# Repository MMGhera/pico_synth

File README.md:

# pico_synth

A small hybrid synthesizer: a Raspberry Pi Pico 2 W generates the waveforms and envelopes digitally, and the sound runs through an analog VCA and filter before reaching the line output.

Designed in KiCad 10. **Status:** PCBs and parts ordered, firmware not written yet. The first version is a single voice.

## How it works

- **Oscillators and envelopes** run in firmware on the RP2350. Sine, square, triangle and sawtooth are selectable, and 4 LEDs show the active waveform.
- **Control voltages** come from an MCP4728 and are level-shifted by a TL074H to drive the OTAs.
- **The analog section** runs from ±5 V generated on the board by a TPS65133 from the Pico's VSYS.
- **8 knobs** (Attack, Decay, Sustain, Release, Cutoff, Resonance, Envelope, Volume) are read through a 74HC4051 mux into the Pico's ADC.
- **Display header** for a 4-pin I²C OLED.
- **Line-level output** for active speakers. There is no onboard power amp.

## Boards

| Board | Layers | Size | Notes |
|---|---|---|---|
| Main (`synth_pico.kicad_pro`) | 4 (GND plane on In1, power on In2) | 160 × 78 mm | Powered over the Pico's USB |
| Keyboard (`keyboard/`) | 2 | ~170 × 105 mm | 12 keys (one octave) + 4 function buttons, Cherry MX–compatible switches, 4×4 diode matrix |

The boards connect through a 10-pin 2.54 mm header and an F-F Dupont ribbon:

| Pin | 1 | 2–5 | 6–9 | 10 |
|---|---|---|---|---|
| Signal | GND | ROW0–3 | COL0–3 | 3V3 (not used by the keyboard) |

The function buttons are octave down, octave up, waveform select, and one spare(will probably implement octave up/down here too).

## Notes

- The pot net names in the schematic (`POT_xxx`) don't match the silkscreen labels. The knob order was changed late, and the knob-to-mux-channel mapping is handled in firmware.
- The BOM lists a PCM5102A, but the PCM5101A (and PCM5100A) are pin-compatible drop-in replacements.

---

made by Mihnea Gherasim

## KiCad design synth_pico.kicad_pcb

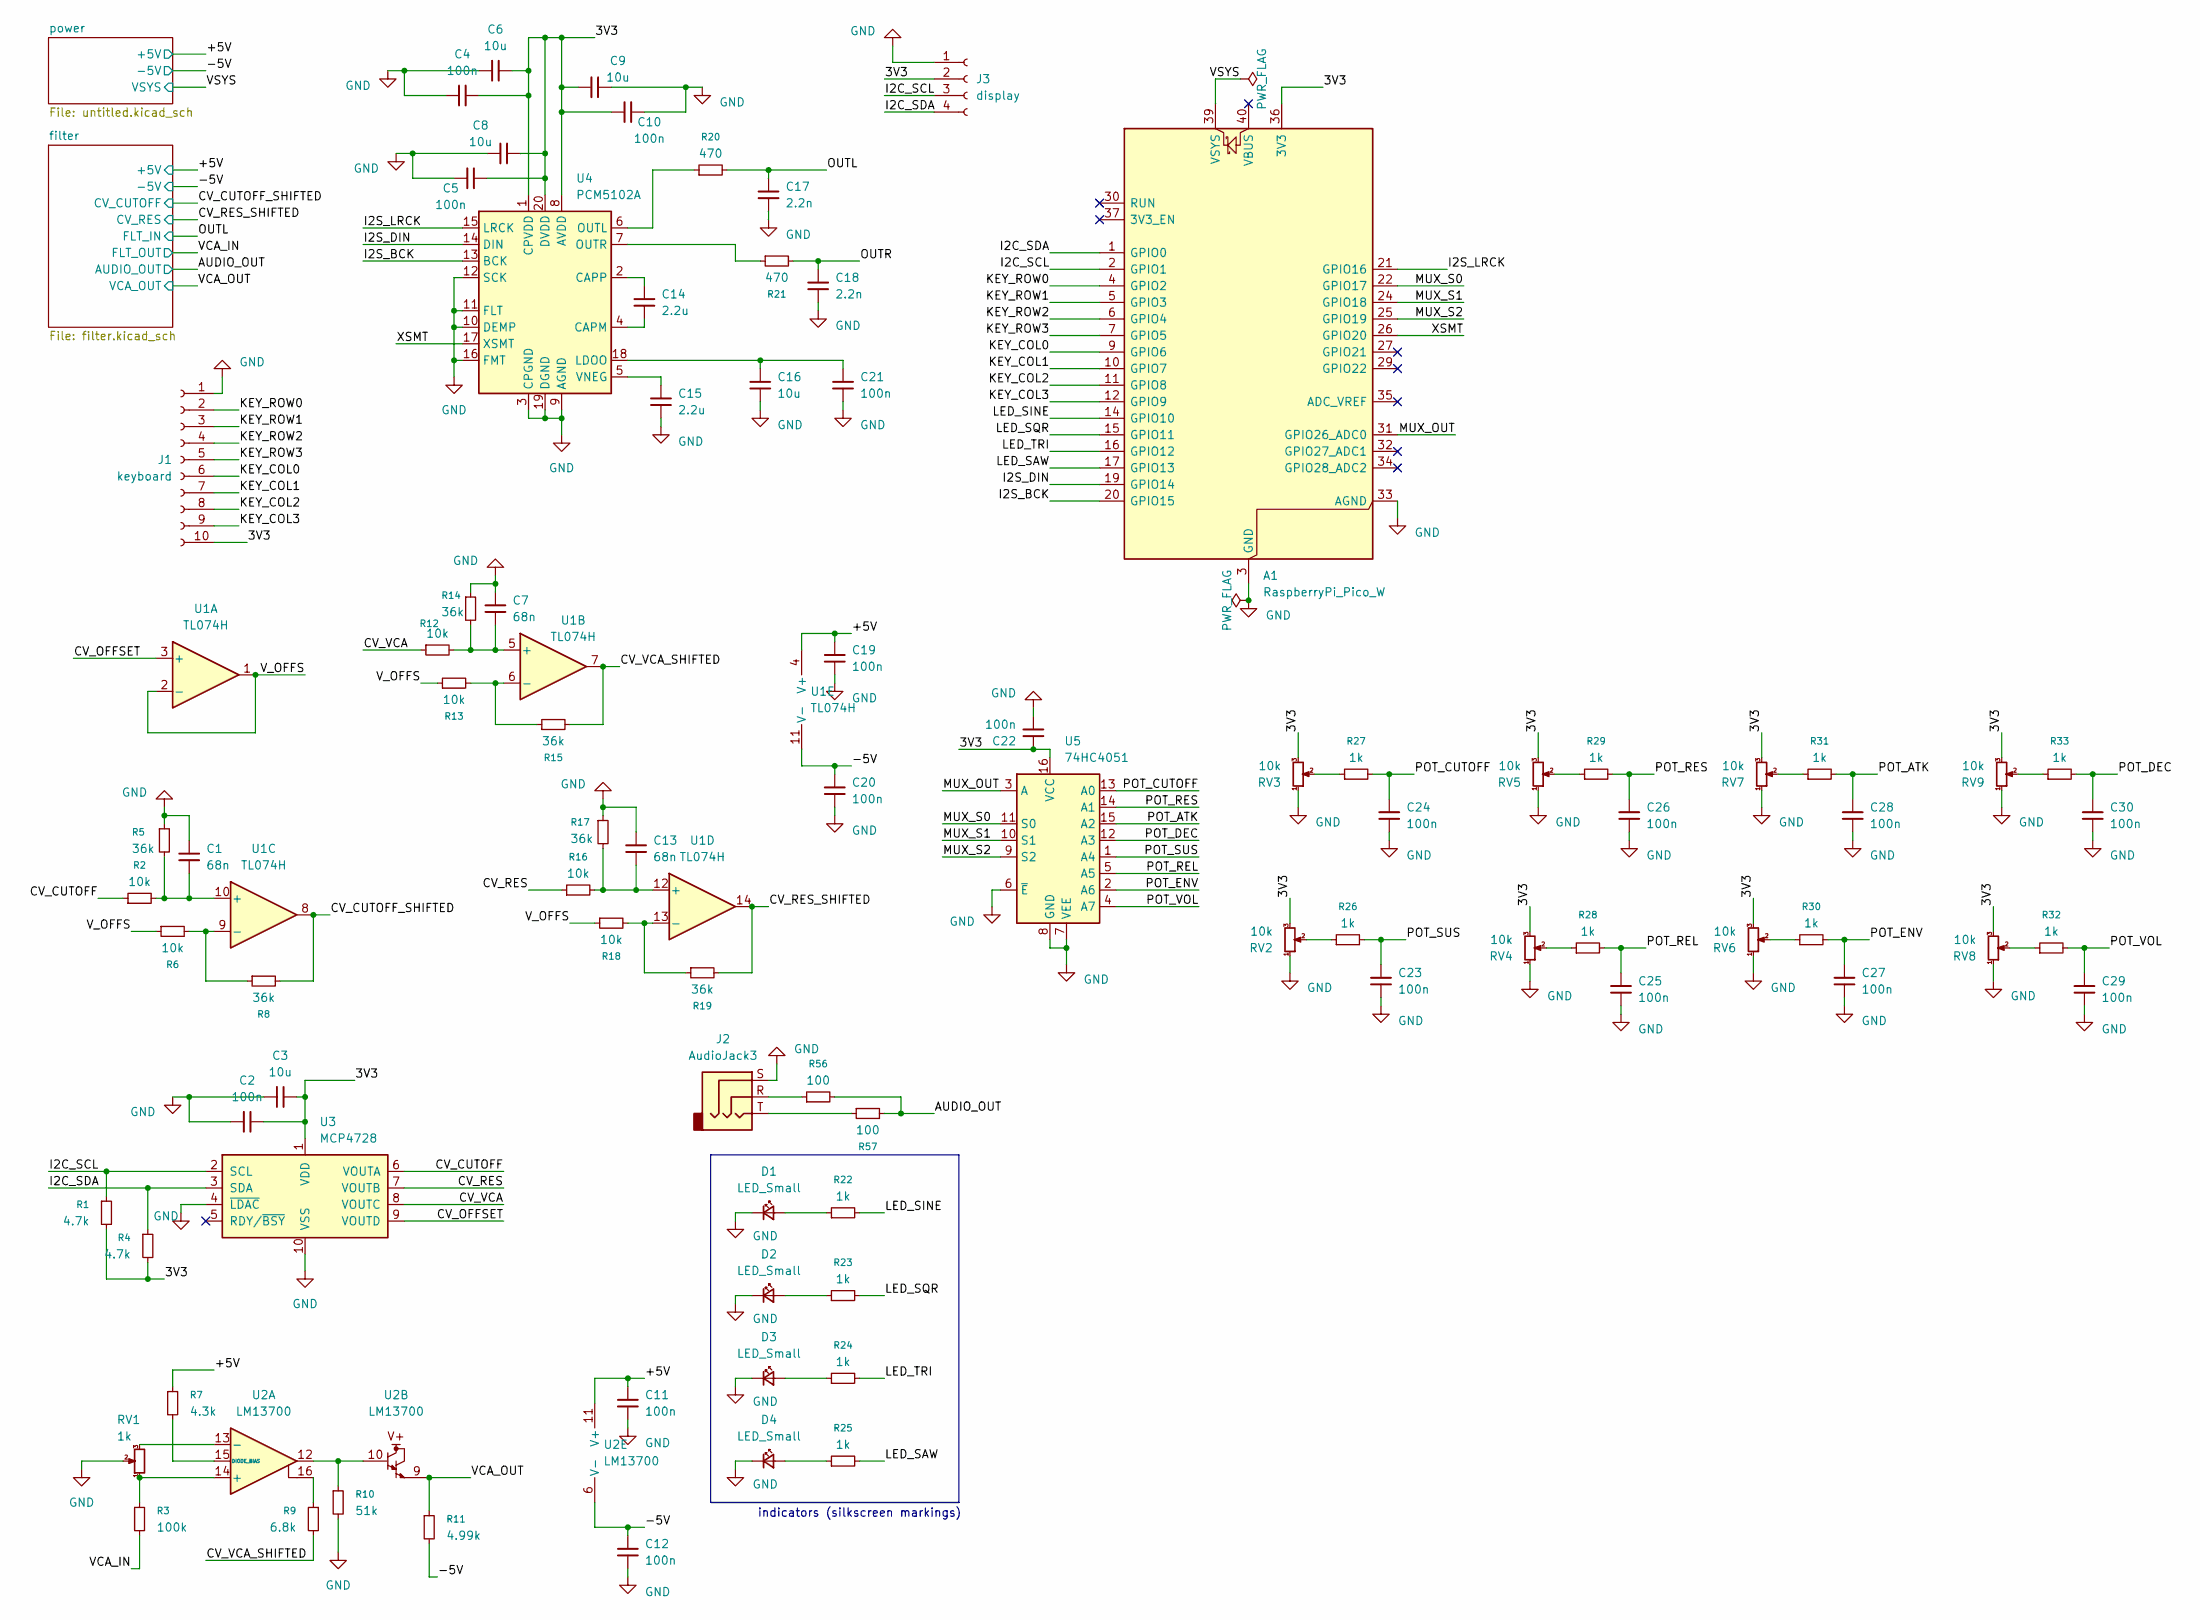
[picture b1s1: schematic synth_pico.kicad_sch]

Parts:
A1: RaspberryPi_Pico_W; RaspberryPi_Pico_W_SMD_HandSolder
C1, C7, C13: 68n; C_0805_2012Metric
C2, C4, C5, C10, C11, C12, C19, C20, C21, C22, C23, C24, C25, C26, C27, C28, C29, C30: 100n; C_0805_2012Metric
C3, C6, C8, C9, C16: 10u; C_0805_2012Metric
C14, C15: 2.2u; C_0805_2012Metric
C17, C18: 2.2n; C_0805_2012Metric
D1, D2, D3, D4: LED_Small; LED_0805_2012Metric
J1: keyboard; PinHeader_1x10_P2.54mm_Vertical
J2: AudioJack3; Jack_3.5mm_CUI_SJ1-3523N_Horizontal
J3: display; PinSocket_1x04_P2.54mm_Vertical
R1, R4: 4.7k; R_0805_2012Metric
R2, R6, R12, R13, R16, R18: 10k; R_0805_2012Metric
R3: 100k; R_0805_2012Metric
R5, R8, R14, R15, R17, R19: 36k; R_0805_2012Metric
R7: 4.3k; R_0805_2012Metric
R9: 6.8k; R_0805_2012Metric
R10: 51k; R_0805_2012Metric
R11: 4.99k; R_0805_2012Metric
R20, R21: 470; R_0805_2012Metric
R22, R23, R24, R25, R26, R27, R28, R29, R30, R31, R32, R33: 1k; R_0805_2012Metric
R56, R57: 100; R_0805_2012Metric
RV1: 1k; Potentiometer_Bourns_3296W_Vertical
RV2, RV3, RV4, RV5, RV6, RV7, RV8, RV9: 10k; Potentiometer_Bourns_PTV09A-1_Single_Vertical
U1: TL074H; TSSOP-14_4.4x5mm_P0.65mm
U2: LM13700; SOIC-16_3.9x9.9mm_P1.27mm
U3: MCP4728; MSOP-10_3x3mm_P0.5mm
U4: PCM5102A; TSSOP-20_4.4x6.5mm_P0.65mm
U5: 74HC4051; SOIC-16_3.9x9.9mm_P1.27mm

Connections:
/3V3: A1.36 (3V3), C2.1, C3.1, C4.1, C5.1, C6.1, C8.1, C9.1, C10.1, C22.1, J1.10, J3.2, R1.2, R4.2, RV2.3, RV3.3, RV4.3, RV5.3, RV6.3, RV7.3, RV8.3, RV9.3, U3.1 (VDD), U4.1 (CPVDD), U4.8 (AVDD), U4.20 (DVDD), U5.16 (VCC)
/+5V: C11.1, C19.1, R7.1, U1.4 (V+), U2.11 (V+); also elsewhere on the board
/-5V: C12.1, C20.1, R11.2, U1.11 (V-), U2.6 (V-); also elsewhere on the board
/AUDIO_OUT: R56.2, R57.2; also elsewhere on the board
/CV_CUTOFF: R2.1, U3.6 (VOUTA)
/CV_CUTOFF_SHIFTED: R8.2, U1.8; also elsewhere on the board
/CV_OFFSET: U1.3 (+), U3.9 (VOUTD)
/CV_RES: R16.1, U3.7 (VOUTB)
/CV_RES_SHIFTED: R19.2, U1.14; also elsewhere on the board
/CV_VCA: R12.1, U3.8 (VOUTC)
/CV_VCA_SHIFTED: R9.2, R15.2, U1.7
/I2C_SCL: A1.2 (GPIO1), J3.3, R1.1, U3.2 (SCL)
/I2C_SDA: A1.1 (GPIO0), J3.4, R4.1, U3.3 (SDA)
/I2S_BCK: A1.20 (GPIO15), U4.13 (BCK)
/I2S_DIN: A1.19 (GPIO14), U4.14 (DIN)
/I2S_LRCK: A1.21 (GPIO16), U4.15 (LRCK)
/KEY_COL0: A1.9 (GPIO6), J1.6
/KEY_COL1: A1.10 (GPIO7), J1.7
/KEY_COL2: A1.11 (GPIO8), J1.8
/KEY_COL3: A1.12 (GPIO9), J1.9
/KEY_ROW0: A1.4 (GPIO2), J1.2
/KEY_ROW1: A1.5 (GPIO3), J1.3
/KEY_ROW2: A1.6 (GPIO4), J1.4
/KEY_ROW3: A1.7 (GPIO5), J1.5
/LED_SAW: A1.17 (GPIO13), R25.2
/LED_SINE: A1.14 (GPIO10), R22.2
/LED_SQR: A1.15 (GPIO11), R23.2
/LED_TRI: A1.16 (GPIO12), R24.2
/MUX_OUT: A1.31 (GPIO26_ADC0), U5.3 (A)
/MUX_S0: A1.22 (GPIO17), U5.11 (S0)
/MUX_S1: A1.24 (GPIO18), U5.10 (S1)
/MUX_S2: A1.25 (GPIO19), U5.9 (S2)
/OUTL: C17.1, R20.2; also elsewhere on the board
/OUTR: C18.1, R21.2
/POT_ATK: C28.1, R31.2, U5.15 (A2)
/POT_CUTOFF: C24.1, R27.2, U5.13 (A0)
/POT_DEC: C30.1, R33.2, U5.12 (A3)
/POT_ENV: C27.1, R30.2, U5.2 (A6)
/POT_REL: C25.1, R28.2, U5.5 (A5)
/POT_RES: C26.1, R29.2, U5.14 (A1)
/POT_SUS: C23.1, R26.2, U5.1 (A4)
/POT_VOL: C29.1, R32.2, U5.4 (A7)
/VCA_IN: R3.2; also elsewhere on the board
/VCA_OUT: R11.1, U2.9; also elsewhere on the board
/VSYS: A1.39 (VSYS); also elsewhere on the board
/V_OFFS: R6.1, R13.1, R18.1, U1.1, U1.2 (-)
/XSMT: A1.26 (GPIO20), U4.17 (XSMT)
GND: A1.3 (GND), A1.8 (GND), A1.13 (GND), A1.18 (GND), A1.23 (GND), A1.28 (GND), A1.33 (AGND), A1.38 (GND), C1.2, C2.2, C3.2, C4.2, C5.2, C6.2, C7.2, C8.2, C9.2, C10.2, C11.2, C12.2, C13.2, C15.2, C16.2, C17.2, C18.2, C19.2, C20.2, C21.2, C22.2, C23.2, C24.2, C25.2, C26.2, C27.2, C28.2, C29.2, C30.2, D1.1 (K), D2.1 (K), D3.1 (K), D4.1 (K), J1.1, J2.S, J3.1, R5.1, R10.2, R14.1, R17.1, RV1.2, RV2.1, RV3.1, RV4.1, RV5.1, RV6.1, RV7.1, RV8.1, RV9.1, U3.4 (~LDAC), U3.10 (VSS), U4.3 (CPGND), U4.9 (AGND), U4.10 (DEMP), U4.11 (FLT), U4.12 (SCK), U4.16 (FMT), U4.19 (DGND), U5.6 (~E), U5.7 (VEE), U5.8 (GND); also elsewhere on the board
unnamed: D1.2 (A), R22.1
unnamed: D2.2 (A), R23.1
unnamed: D3.2 (A), R24.1
unnamed: D4.2 (A), R25.1
unnamed: J2.R, R56.1
unnamed: J2.T, R57.1
unnamed: R9.1, U2.16
unnamed: R10.1, U2.10, U2.12
unnamed: R26.1, RV2.2
unnamed: R27.1, RV3.2
unnamed: R28.1, RV4.2
unnamed: R29.1, RV5.2
unnamed: R30.1, RV6.2
unnamed: R31.1, RV7.2
unnamed: R32.1, RV8.2
unnamed: R33.1, RV9.2
unnamed: C7.1, R12.2, R14.2, U1.5 (+)
unnamed: R13.2, R15.1, U1.6 (-)
unnamed: C1.1, R2.2, R5.2, U1.10 (+)
unnamed: R6.2, R8.1, U1.9 (-)
unnamed: C13.1, R16.2, R17.2, U1.12 (+)
unnamed: R18.2, R19.1, U1.13 (-)
unnamed: R3.1, RV1.1, U2.14 (+)
unnamed: RV1.3, U2.13 (-)
unnamed: R7.2, U2.15 (DIODE_BIAS)
unnamed: C14.2, U4.4 (CAPM)
unnamed: C14.1, U4.2 (CAPP)
unnamed: C16.1, C21.1, U4.18 (LDOO)
unnamed: R20.1, U4.6 (OUTL)
unnamed: R21.1, U4.7 (OUTR)
unnamed: C15.1, U4.5 (VNEG)

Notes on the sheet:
indicators (silkscreen markings)

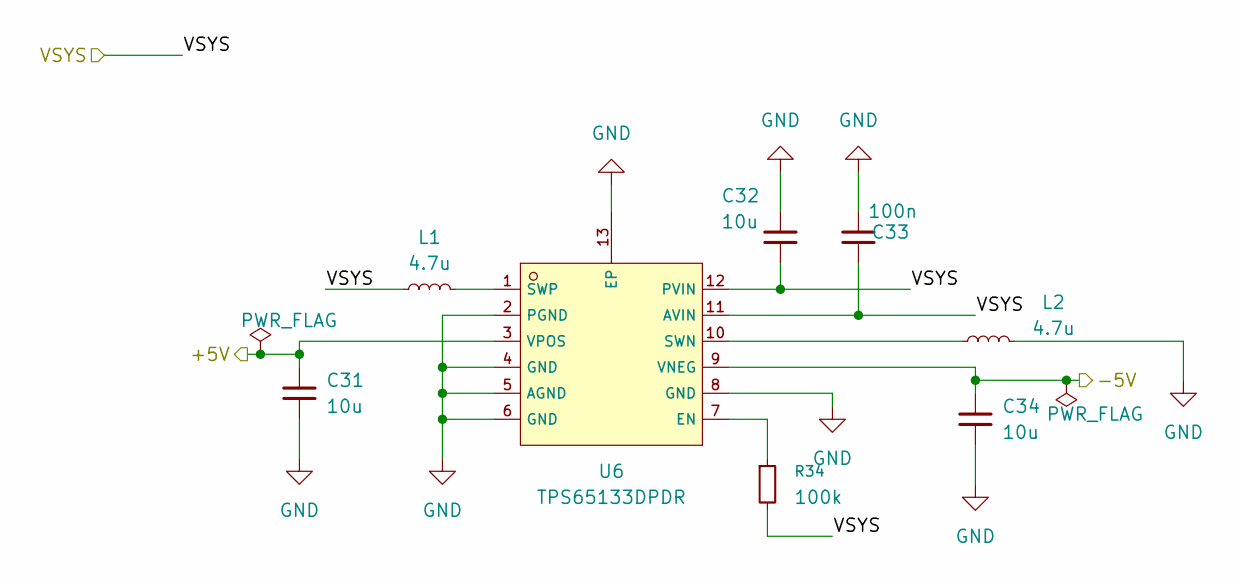
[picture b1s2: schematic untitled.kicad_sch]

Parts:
C31, C32, C34: 10u; C_0805_2012Metric
C33: 100n; C_0805_2012Metric
L1, L2: 4.7u; L_1008_2520Metric
R34: 100k; R_0805_2012Metric
U6: TPS65133DPDR; Texas_DPD0012A_WSON-12-1EP_3x3mm_P0.45mm; LCSC C134100

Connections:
/+5V: C31.1, U6.3 (VPOS); also elsewhere on the board
/-5V: C34.1, U6.9 (VNEG); also elsewhere on the board
/VSYS: C32.1, C33.1, L1.1, R34.2, U6.11 (AVIN), U6.12 (PVIN); also elsewhere on the board
GND: C31.2, C32.2, C33.2, C34.2, L2.2, U6.2 (PGND), U6.4 (GND), U6.5 (AGND), U6.6 (GND), U6.8 (GND), U6.13 (EP); also elsewhere on the board
unnamed: R34.1, U6.7 (EN)
unnamed: L2.1, U6.10 (SWN)
unnamed: L1.2, U6.1 (SWP)

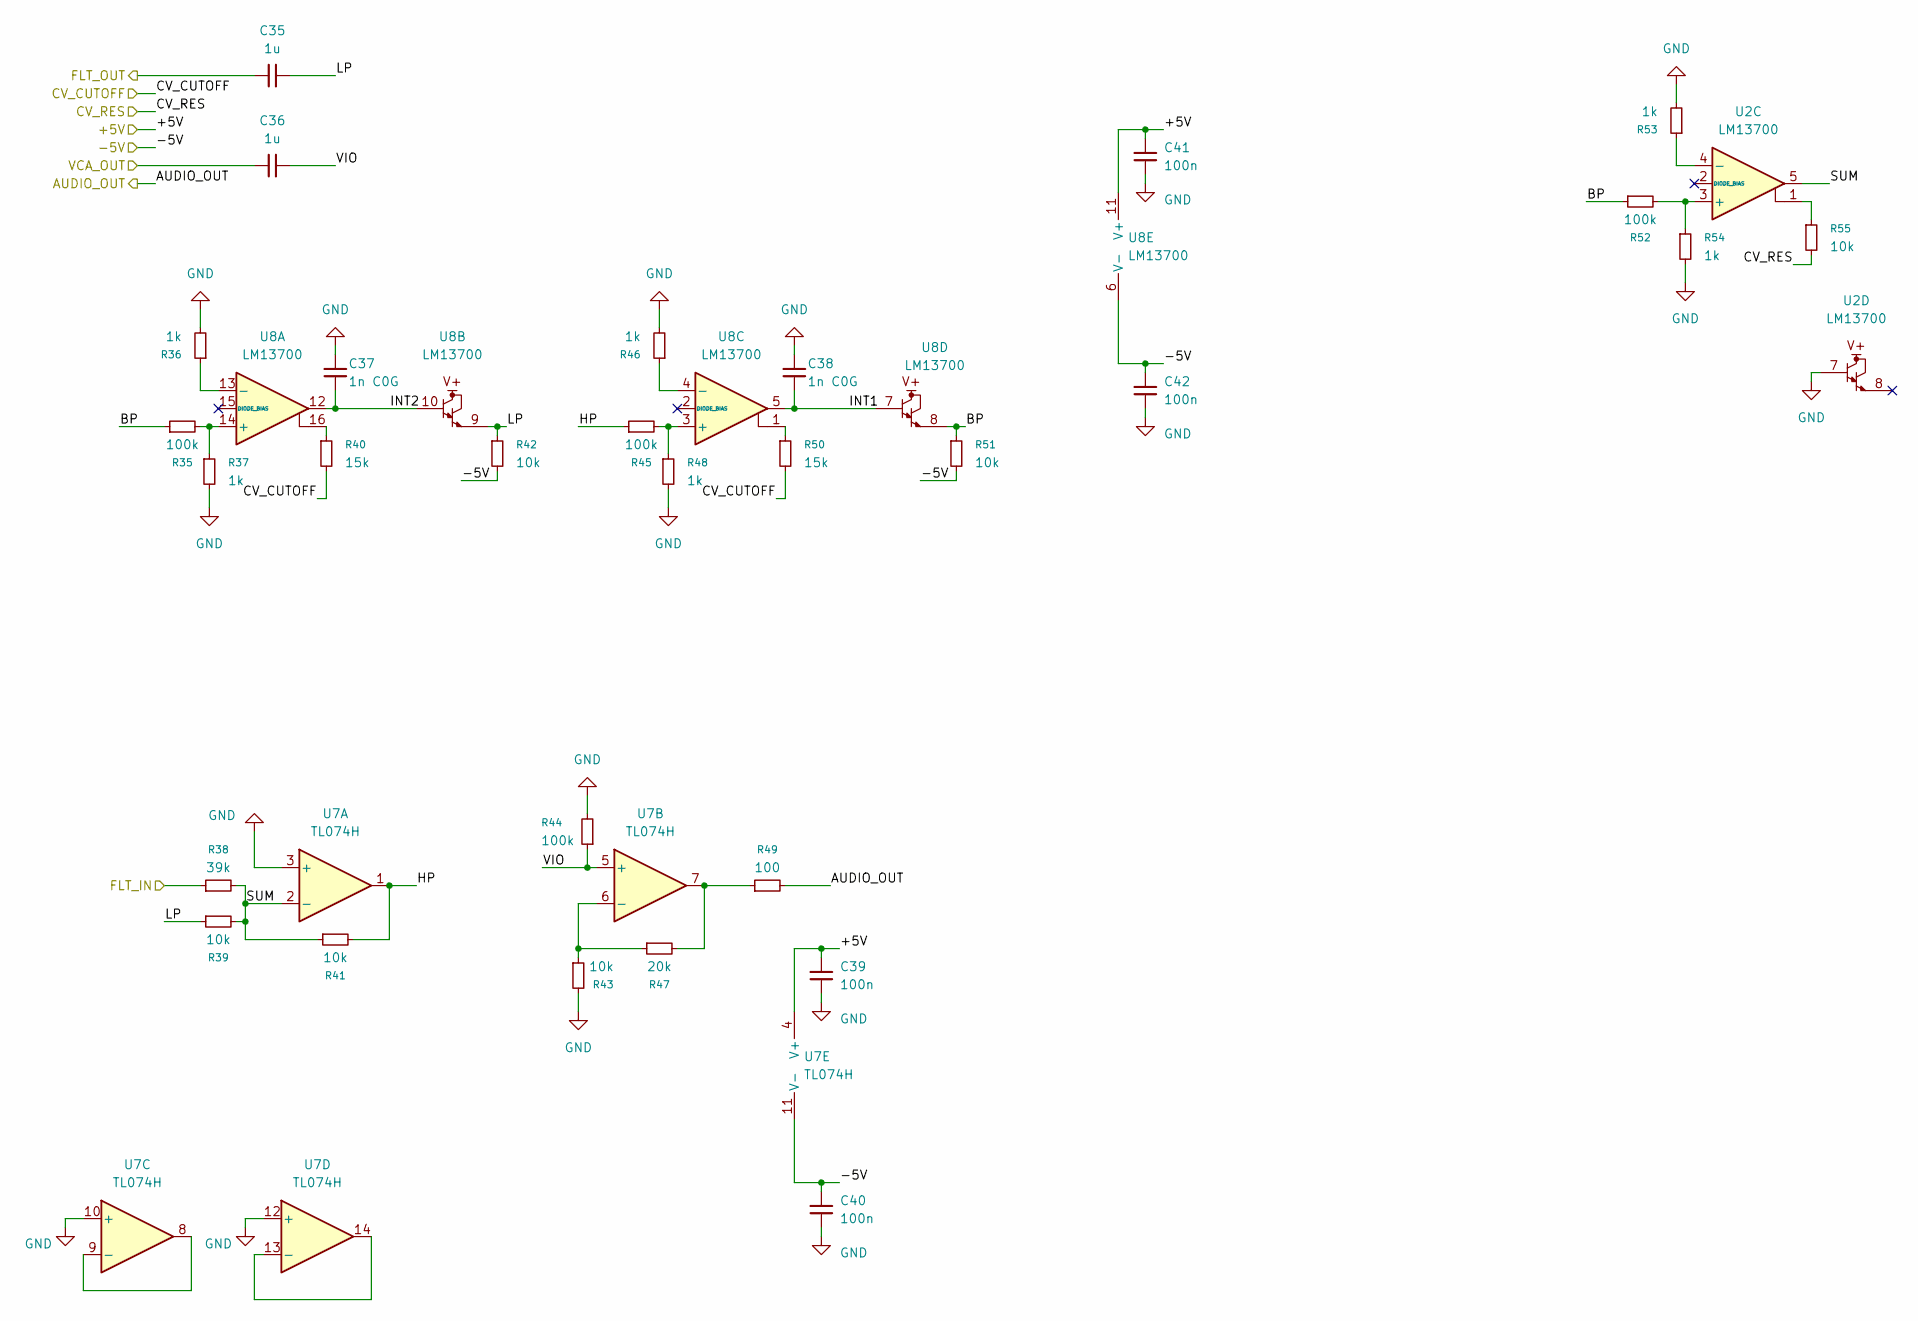
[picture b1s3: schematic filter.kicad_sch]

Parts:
C35, C36: 1u; C_0805_2012Metric
C37, C38: 1n C0G; C_0805_2012Metric
C39, C40, C41, C42: 100n; C_0805_2012Metric
R35, R44, R45, R52: 100k; R_0805_2012Metric
R36, R37, R46, R48, R53, R54: 1k; R_0805_2012Metric
R38: 39k; R_0805_2012Metric
R39, R41, R42, R43, R51, R55: 10k; R_0805_2012Metric
R40, R50: 15k; R_0805_2012Metric
R47: 20k; R_0805_2012Metric
R49: 100; R_0805_2012Metric
U2, U8: LM13700; SOIC-16_3.9x9.9mm_P1.27mm
U7: TL074H; TSSOP-14_4.4x5mm_P0.65mm

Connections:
/+5V: C39.1, C41.1, U7.4 (V+), U8.11 (V+); also elsewhere on the board
/-5V: C40.1, C42.1, R42.2, R51.2, U7.11 (V-), U8.6 (V-); also elsewhere on the board
/AUDIO_OUT: R49.2; also elsewhere on the board
/CV_CUTOFF_SHIFTED: R40.2, R50.2; also elsewhere on the board
/CV_RES_SHIFTED: R55.2; also elsewhere on the board
/OUTL: R38.1; also elsewhere on the board
/VCA_IN: C35.1; also elsewhere on the board
/VCA_OUT: C36.1; also elsewhere on the board
/filter/BP: R35.1, R51.1, R52.1, U8.8
/filter/HP: R41.2, R45.1, U7.1
/filter/INT1: C38.2, U8.5, U8.7
/filter/INT2: C37.2, U8.10, U8.12
/filter/LP: C35.2, R39.1, R42.1, U8.9
/filter/SUM: R38.2, R39.2, R41.1, U2.5, U7.2 (-)
/filter/VIO: C36.2, R44.1, U7.5 (+)
GND: C37.1, C38.1, C39.2, C40.2, C41.2, C42.2, R36.2, R37.2, R43.2, R44.2, R46.2, R48.2, R53.2, R54.2, U2.7, U7.3 (+), U7.10 (+), U7.12 (+); also elsewhere on the board
unnamed: R40.1, U8.16
unnamed: R47.2, R49.1, U7.7
unnamed: R50.1, U8.1
unnamed: R55.1, U2.1
unnamed: R52.2, R54.1, U2.3 (+)
unnamed: R53.1, U2.4 (-)
unnamed: R43.1, R47.1, U7.6 (-)
unnamed: U7.8, U7.9 (-)
unnamed: U7.13 (-), U7.14
unnamed: R35.2, R37.1, U8.14 (+)
unnamed: R36.1, U8.13 (-)
unnamed: R45.2, R48.1, U8.3 (+)
unnamed: R46.1, U8.4 (-)

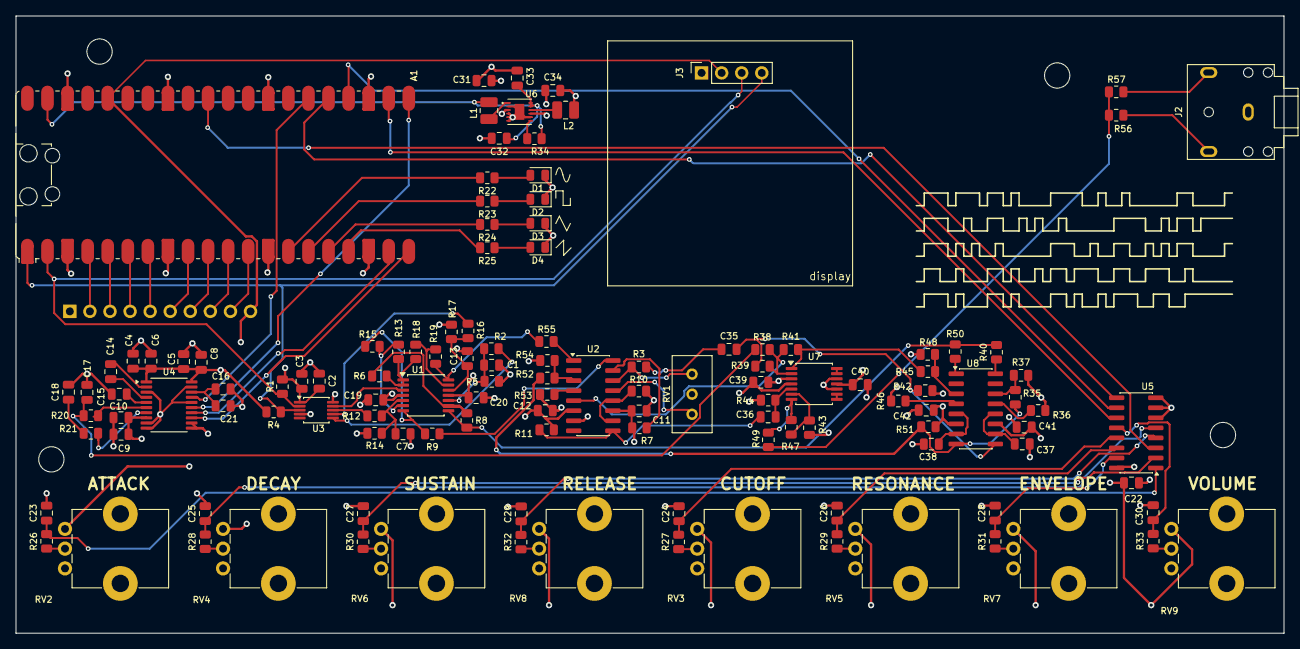
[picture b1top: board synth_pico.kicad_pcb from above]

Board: 4 copper layers, 160.4 x 78.1 mm, 130 parts (1 on the bottom side), 102 nets.

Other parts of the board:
H1, H2, H3, H4: MountingHole_3.2mm_M3

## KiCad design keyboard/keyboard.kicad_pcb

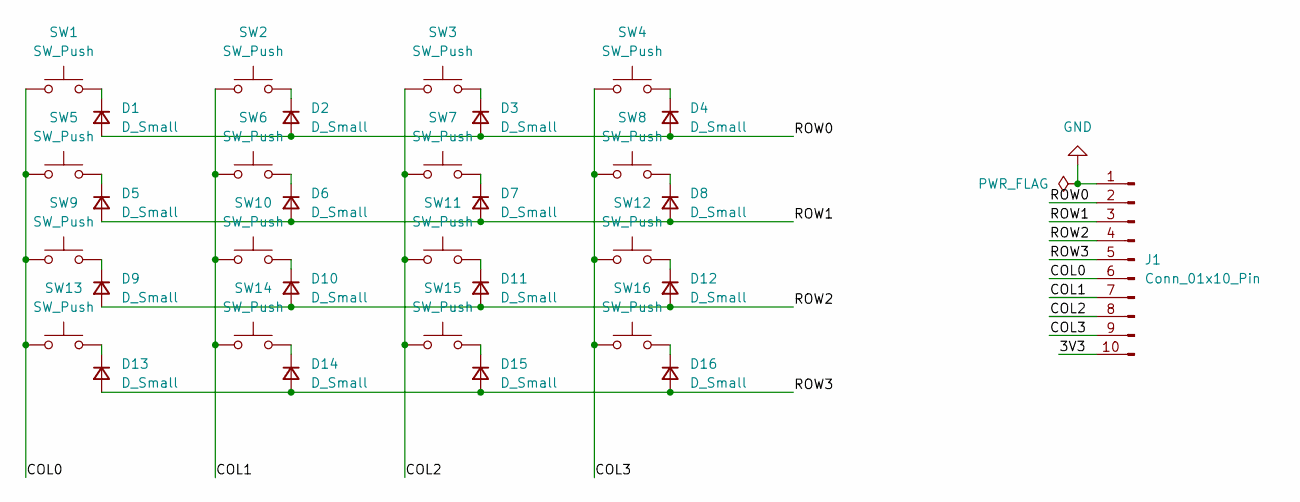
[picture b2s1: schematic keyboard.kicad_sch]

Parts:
D1, D2, D3, D4, D5, D6, D7, D8, D9, D10, D11, D12, D13, D14, D15, D16: D_Small; D_SOD-123
J1: Conn_01x10_Pin; PinHeader_1x10_P2.54mm_Horizontal
SW1, SW2, SW3, SW4, SW5, SW6, SW7, SW8, SW9, SW10, SW11, SW12, SW13, SW14, SW15, SW16: SW_Push; SW_Cherry_MX_1.00u_PCB

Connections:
/3V3: J1.10
/COL0: J1.6, SW1.1, SW5.1, SW9.1, SW13.1
/COL1: J1.7, SW2.1, SW6.1, SW10.1, SW14.1
/COL2: J1.8, SW3.1, SW7.1, SW11.1, SW15.1
/COL3: J1.9, SW4.1, SW8.1, SW12.1, SW16.1
/ROW0: D1.2 (A), D2.2 (A), D3.2 (A), D4.2 (A), J1.2
/ROW1: D5.2 (A), D6.2 (A), D7.2 (A), D8.2 (A), J1.3
/ROW2: D9.2 (A), D10.2 (A), D11.2 (A), D12.2 (A), J1.4
/ROW3: D13.2 (A), D14.2 (A), D15.2 (A), D16.2 (A), J1.5
GND: J1.1
unnamed: D1.1 (K), SW1.2
unnamed: D2.1 (K), SW2.2
unnamed: D3.1 (K), SW3.2
unnamed: D4.1 (K), SW4.2
unnamed: D5.1 (K), SW5.2
unnamed: D6.1 (K), SW6.2
unnamed: D7.1 (K), SW7.2
unnamed: D8.1 (K), SW8.2
unnamed: D9.1 (K), SW9.2
unnamed: D10.1 (K), SW10.2
unnamed: D11.1 (K), SW11.2
unnamed: D12.1 (K), SW12.2
unnamed: D13.1 (K), SW13.2
unnamed: D14.1 (K), SW14.2
unnamed: D15.1 (K), SW15.2
unnamed: D16.1 (K), SW16.2

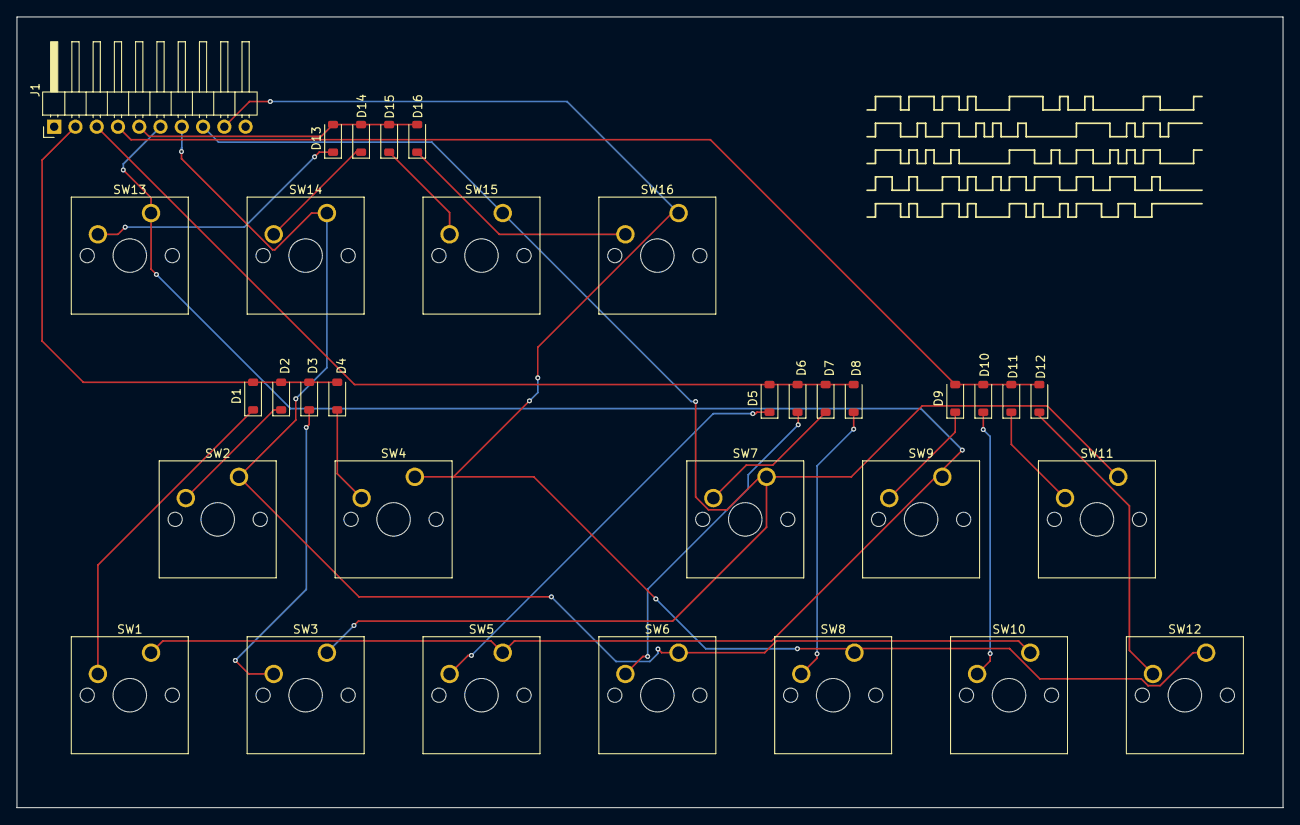
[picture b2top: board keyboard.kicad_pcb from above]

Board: 2 copper layers, 151.2 x 94.4 mm, 33 parts (0 on the bottom side), 24 nets.
